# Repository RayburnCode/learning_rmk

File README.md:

<!-- @format -->

# Keyboard based off RMK and Mad Mod Labs 68 key keyboard

## Thank you

- [RMK](https://rmk.rs/index.html) for the keyboard firmware and inspiration
- [Mad Mod labs](https://www.printables.com/model/307908-mechanical-keyboard-68-key-65/files) for the 3D printable case design
- [Mad Mod Labs Youtube](https://www.youtube.com/watch?v=iOeYkLlq9Ds&t=628s)
- [Keyboard Layout Editor](https://www.keyboard-layout-editor.com)
- [Keys Kicad](https://github.com/perigoso/keyswitch-kicad-library)
- Plate and Case Builders:
- - [Keeb](https://plate.keeb.io)
- - [Swillkb](http://builder.swillkb.com)

## Flashing Firmware to MCU

- [Probe-rs](https://probe.rs)

cargo-flash vs cargo-embed

### hex

```bash
probe-rs download --format hex --chip <YourMCUChip> your_firmware.hex
```

### uf2

Drag and drop tools/Mad_Mod_Labs_68.uf2 into the folder.

1. Hold the BOOTSEL (or BOOT) button: Press and hold the BOOTSEL button on your board. While holding it, plug the USB cable into your Mac. Keep holding the button for a few seconds after connecting, then release .

2. Use the RESET and BOOT buttons: Press and hold the BOOT button. While holding it, press and release the RESET button. Then, release the BOOT button .

3. Double-tap RESET: Quickly press the RESET button twice

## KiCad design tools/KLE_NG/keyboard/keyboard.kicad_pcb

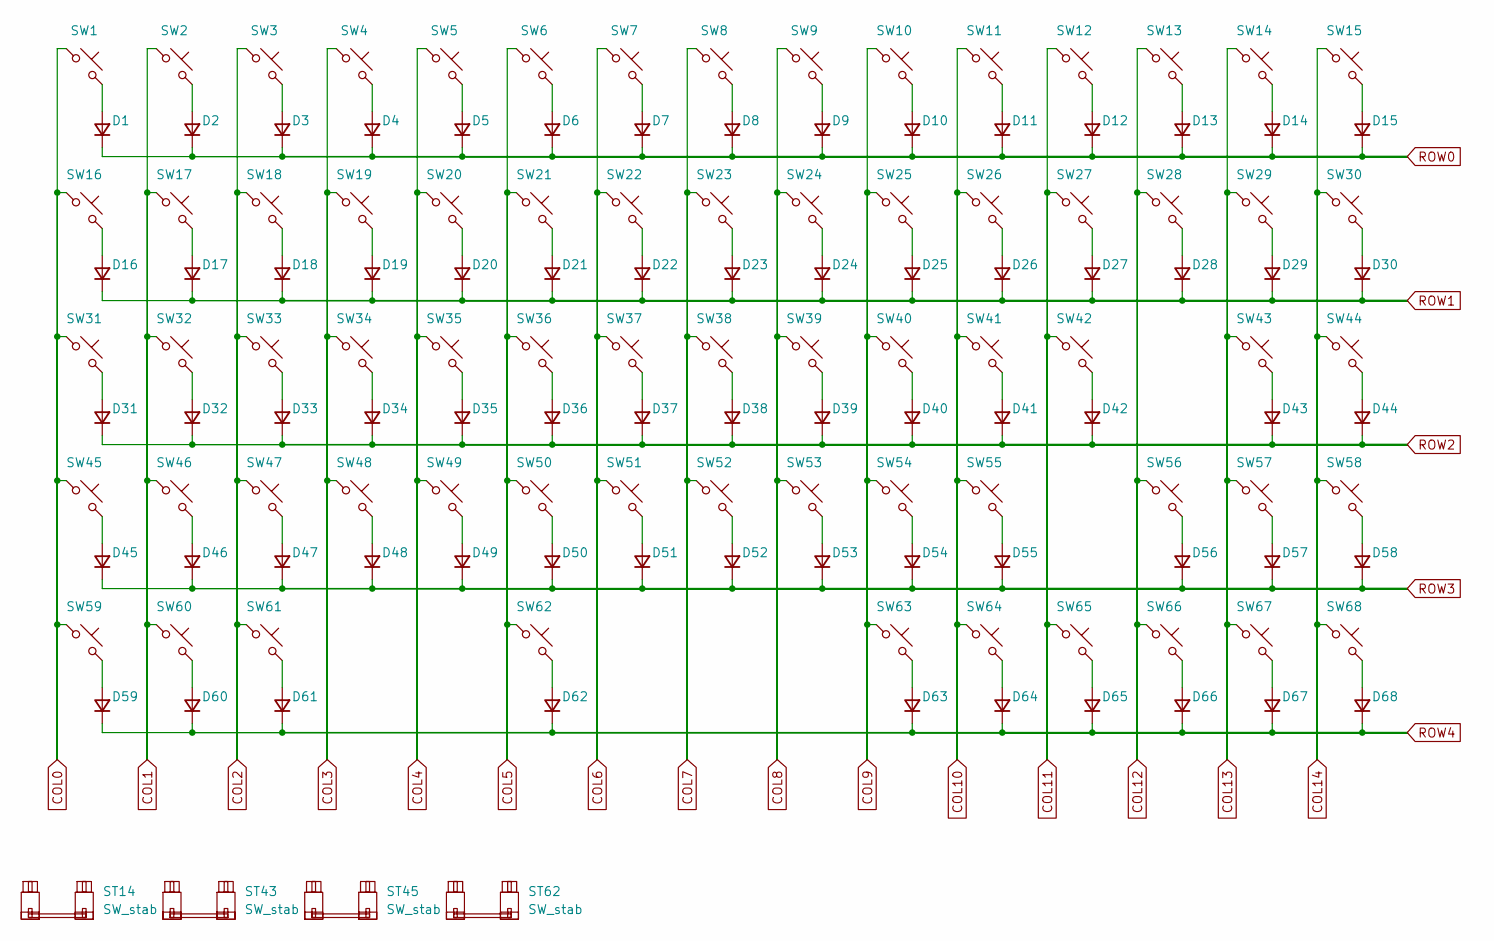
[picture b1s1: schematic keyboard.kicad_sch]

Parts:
D1, D2, D3, D4, D5, D6, D7, D8, D9, D10, D11, D12, D13, D14, D15, D16, D17, D18, D19, D20, D21, D22, D23, D24, D25, D26, D27, D28, D29, D30, D31, D32, D33, D34, D35, D36, D37, D38, D39, D40, D41, D42, D43, D44, D45, D46, D47, D48, D49, D50, D51, D52, D53, D54, D55, D56, D57, D58, D59, D60, D61, D62, D63, D64, D65, D66, D67, D68: D; D_SOD-123F
ST14, ST43, ST45: SW_stab; Stabilizer_Cherry_MX_2.00u
ST62: SW_stab; Stabilizer_Cherry_MX_6.25u
SW1, SW2, SW3, SW4, SW5, SW6, SW7, SW8, SW9, SW10, SW11, SW12, SW13, SW15, SW17, SW18, SW19, SW20, SW21, SW22, SW23, SW24, SW25, SW26, SW27, SW28, SW30, SW32, SW33, SW34, SW35, SW36, SW37, SW38, SW39, SW40, SW41, SW42, SW44, SW46, SW47, SW48, SW49, SW50, SW51, SW52, SW53, SW54, SW55, SW57, SW58, SW63, SW64, SW65, SW66, SW67, SW68: SW_Push; SW_Cherry_MX_PCB_1.00u
SW14: SW_Push; SW_Cherry_MX_PCB_2.00u
SW16, SW29: SW_Push; SW_Cherry_MX_PCB_1.50u
SW31, SW56: SW_Push; SW_Cherry_MX_PCB_1.75u
SW43, SW45: SW_Push; SW_Cherry_MX_PCB_2.25u
SW59, SW60, SW61: SW_Push; SW_Cherry_MX_PCB_1.25u
SW62: SW_Push; SW_Cherry_MX_PCB_6.25u

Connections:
COL0: SW1.1, SW16.1, SW31.1, SW45.1, SW59.1
COL1: SW2.1, SW17.1, SW32.1, SW46.1, SW60.1
COL2: SW3.1, SW18.1, SW33.1, SW47.1, SW61.1
COL3: SW4.1, SW19.1, SW34.1, SW48.1
COL4: SW5.1, SW20.1, SW35.1, SW49.1
COL5: SW6.1, SW21.1, SW36.1, SW50.1, SW62.1
COL6: SW7.1, SW22.1, SW37.1, SW51.1
COL7: SW8.1, SW23.1, SW38.1, SW52.1
COL8: SW9.1, SW24.1, SW39.1, SW53.1
COL9: SW10.1, SW25.1, SW40.1, SW54.1, SW63.1
COL10: SW11.1, SW26.1, SW41.1, SW55.1, SW64.1
COL11: SW12.1, SW27.1, SW42.1, SW65.1
COL12: SW13.1, SW28.1, SW56.1, SW66.1
COL13: SW14.1, SW29.1, SW43.1, SW57.1, SW67.1
COL14: SW15.1, SW30.1, SW44.1, SW58.1, SW68.1
unnamed: D1.2 (A), SW1.2
unnamed: D2.2 (A), SW2.2
unnamed: D3.2 (A), SW3.2
unnamed: D4.2 (A), SW4.2
unnamed: D5.2 (A), SW5.2
unnamed: D6.2 (A), SW6.2
unnamed: D7.2 (A), SW7.2
unnamed: D8.2 (A), SW8.2
unnamed: D9.2 (A), SW9.2
unnamed: D10.2 (A), SW10.2
unnamed: D11.2 (A), SW11.2
unnamed: D12.2 (A), SW12.2
unnamed: D13.2 (A), SW13.2
unnamed: D14.2 (A), SW14.2
unnamed: D15.2 (A), SW15.2
unnamed: D16.2 (A), SW16.2
unnamed: D17.2 (A), SW17.2
unnamed: D18.2 (A), SW18.2
unnamed: D19.2 (A), SW19.2
unnamed: D20.2 (A), SW20.2
unnamed: D21.2 (A), SW21.2
unnamed: D22.2 (A), SW22.2
unnamed: D23.2 (A), SW23.2
unnamed: D24.2 (A), SW24.2
unnamed: D25.2 (A), SW25.2
unnamed: D26.2 (A), SW26.2
unnamed: D27.2 (A), SW27.2
unnamed: D28.2 (A), SW28.2
unnamed: D29.2 (A), SW29.2
unnamed: D30.2 (A), SW30.2
unnamed: D31.2 (A), SW31.2
unnamed: D32.2 (A), SW32.2
unnamed: D33.2 (A), SW33.2
unnamed: D34.2 (A), SW34.2
unnamed: D35.2 (A), SW35.2
unnamed: D36.2 (A), SW36.2
unnamed: D37.2 (A), SW37.2
unnamed: D38.2 (A), SW38.2
unnamed: D39.2 (A), SW39.2
unnamed: D40.2 (A), SW40.2
unnamed: D41.2 (A), SW41.2
unnamed: D42.2 (A), SW42.2
unnamed: D43.2 (A), SW43.2
unnamed: D44.2 (A), SW44.2
unnamed: D45.2 (A), SW45.2
unnamed: D46.2 (A), SW46.2
unnamed: D47.2 (A), SW47.2
unnamed: D48.2 (A), SW48.2
unnamed: D49.2 (A), SW49.2
unnamed: D50.2 (A), SW50.2
unnamed: D51.2 (A), SW51.2
unnamed: D52.2 (A), SW52.2
unnamed: D53.2 (A), SW53.2
unnamed: D54.2 (A), SW54.2
unnamed: D55.2 (A), SW55.2
unnamed: D56.2 (A), SW56.2
unnamed: D57.2 (A), SW57.2
unnamed: D58.2 (A), SW58.2
unnamed: D59.2 (A), SW59.2
unnamed: D60.2 (A), SW60.2
unnamed: D61.2 (A), SW61.2
unnamed: D62.2 (A), SW62.2
unnamed: D63.2 (A), SW63.2
unnamed: D64.2 (A), SW64.2
unnamed: D65.2 (A), SW65.2
unnamed: D66.2 (A), SW66.2
unnamed: D67.2 (A), SW67.2
unnamed: D68.2 (A), SW68.2
ROW0: D1.1 (K), D2.1 (K), D3.1 (K), D4.1 (K), D5.1 (K), D6.1 (K), D7.1 (K), D8.1 (K), D9.1 (K), D10.1 (K), D11.1 (K), D12.1 (K), D13.1 (K), D14.1 (K), D15.1 (K)
ROW1: D16.1 (K), D17.1 (K), D18.1 (K), D19.1 (K), D20.1 (K), D21.1 (K), D22.1 (K), D23.1 (K), D24.1 (K), D25.1 (K), D26.1 (K), D27.1 (K), D28.1 (K), D29.1 (K), D30.1 (K)
ROW2: D31.1 (K), D32.1 (K), D33.1 (K), D34.1 (K), D35.1 (K), D36.1 (K), D37.1 (K), D38.1 (K), D39.1 (K), D40.1 (K), D41.1 (K), D42.1 (K), D43.1 (K), D44.1 (K)
ROW3: D45.1 (K), D46.1 (K), D47.1 (K), D48.1 (K), D49.1 (K), D50.1 (K), D51.1 (K), D52.1 (K), D53.1 (K), D54.1 (K), D55.1 (K), D56.1 (K), D57.1 (K), D58.1 (K)
ROW4: D59.1 (K), D60.1 (K), D61.1 (K), D62.1 (K), D63.1 (K), D64.1 (K), D65.1 (K), D66.1 (K), D67.1 (K), D68.1 (K)

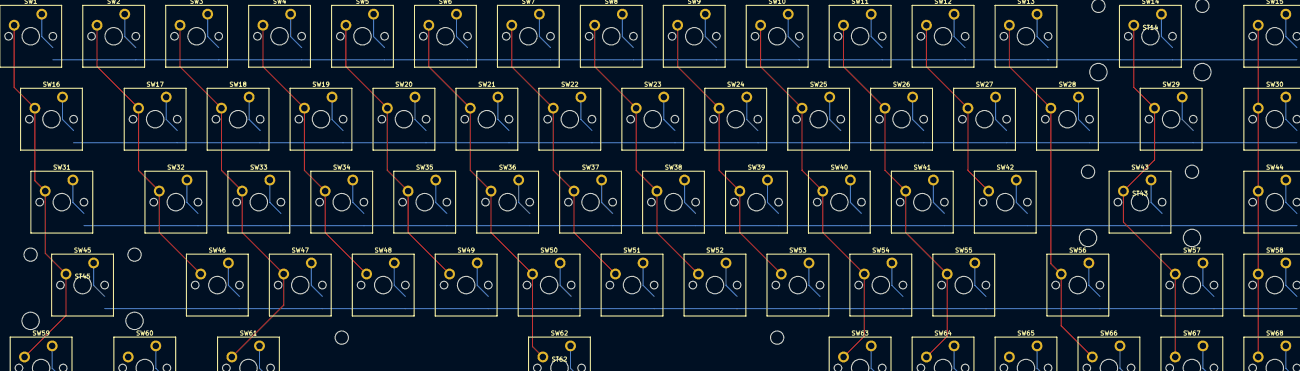
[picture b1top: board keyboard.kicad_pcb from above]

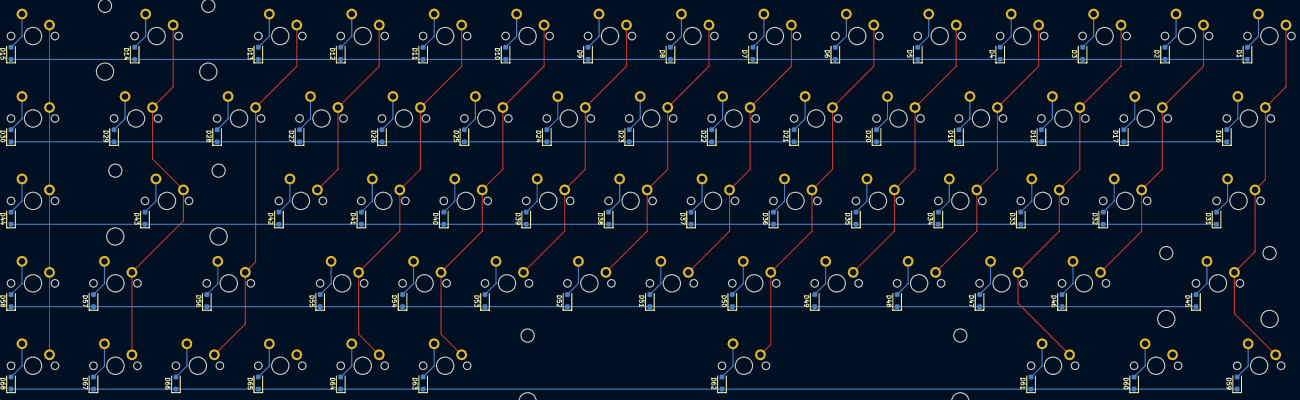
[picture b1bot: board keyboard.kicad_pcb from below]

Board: 2 copper layers, 140 parts (68 on the bottom side), 88 nets.

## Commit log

2025-10-29 Update keyboard layout configuration
2025-10-29 Remove redundant product_name from keyboard.toml
    Removed redundant product_name entry from keyboard configuration.
2025-10-29 Refactor keymap section in keyboard.toml
    Updated keymap format in keyboard.toml
2025-10-29 Refactor keyboard layout configuration
    Updated keymap structure and removed legacy layout.
2025-10-29 Rename input and output pins in keyboard.toml
2025-10-29 Update keymap for keyboard layout
2025-10-29 Fix formatting in keyboard.toml
2025-10-29 Fix typo in keyboard.toml for PageUp/PageDown
2025-10-30 Add README with keyboard project details
2026-03-19 bump
2026-03-19 updating Readme
2026-04-13 updated based off KLE_NG
2026-04-13 fixing fn error
2026-04-13 redoing rows
